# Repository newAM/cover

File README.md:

# Cover

A controller to automate my window shades.

This project is from late 2020; much older than the commit dates indicate.  I revisited it to migrate the raspberry pi controller to NixOS and decided to document the project.

## Software

* [NixOS](https://nixos.org/) for the raspberry pi OS
* [KiCad](https://www.kicad.org/) (version 5) for PCB design
* [OpenSCAD](https://openscad.org/) for 3D printed parts

## Hardware

The hardware consists of:

* A raspberry pi
* A custom pi hat to drive motors
* A motor per shade
* Plastic 3D printed motor mounts
* Metal 3D printed grips
* Plastic 3D printed guides
* 2 reed switches on each shade for endstops

### Shades

The shades on my windows have a continuous ball chain string without any clasps.  The ball chain originally had some plastic stoppers on them, but these all broke off before this project due to UV exposure.

The windows have a clutch on them, I measured the force required to overcome this clutch by tieing a water bottle onto the ball chain, and filling it with water until the chain started to move.  The final weight of the water bottle was 2 kilos ∴ about 20N of force is required to move the shades.

### Motors

I purchased generic 12V motors online, if you search "DC 12V worm gear motor" you will find these easily at almost every retailer.  These had more than enough torque to overcome the 20N of the clutch.

I purchased 25 rpm motors, which was lower than I needed.  The grips ended up being a smaller diameter than I initially intended; which means the shades move slower than intended.

#### Grips

The grip is a metal 3D printed part with grooves for the ball chain.  I tried to make this in plastic, but the forces required always stripped plastic parts.

The intent was to make this part match the diameter of the clutch on my shades, but metal 3D printing is extremely expensive, and I ended up making the part much smaller to keep costs down.  Each part ended up costing $40 from [shapeways](https://www.shapeways.com/).

#### Mount

The mount screws onto the motor and has two large flat surfaces to mount the motor onto the wall with command strips.  I used command strips because I rent, but they were probably the best solution anyway.

### Endstops

The endstops consisted of two reed switches per window, one at the top of the frame, and one at the bottom.  I taped magnets onto the shades to trip the reed switches when the shades hit the limit.

3D printed mounts were necessary to raise the reed switches to the shades.

### Controller

The controller is just a hat on a raspberry pi with 6x inputs for reed switches, and 3x DRV8871DDAR motor drivers for the output.

If I had to do this project over I would have used an Ethernet connected microcontroller instead of a pi.  Upon boot the raspberry pi takes a few seconds to apply the GPIO configuration in `/boot/config.txt`, which is not desirable, as this can lead to the shades moving beyond their endstop positions.

The controller takes commands over MQTT for move up, move down, and stop.

I run [NixOS](https://nixos.org/) on the pi.  The only other configuration necessary is putting `gpio=5,12,6,13,19,16=op,dl` into `/boot/config.txt`:

```nix
{
  boot.loader.raspberryPi = {
    enable = true;
    version = n;
    firmwareConfig = ''
      gpio=5,12,6,13,19,16=op,dl
    '';
  };
}
```

The service is a simple python script that I am not very proud of because it is all blocking code with polling.  I plan to rewrite this at some point, but it keeps working so I keep putting it off.

## Home Assistant

Home-assistant has a [MQTT cover integration](https://www.home-assistant.io/integrations/cover.mqtt/) that works out of the box.

```nix
{
  services.home-assistant.config.cover = [
    {
      platform = "mqtt";
      name = "Middle Window";
      unique_id = "middle_window";
      command_topic = "/home/sunroom/middle_window/set";
      position_topic = "/home/sunroom/middle_window/position";
      optimistic = false;
      retain = false;
    }
    # ... other shades
  ];
}
```

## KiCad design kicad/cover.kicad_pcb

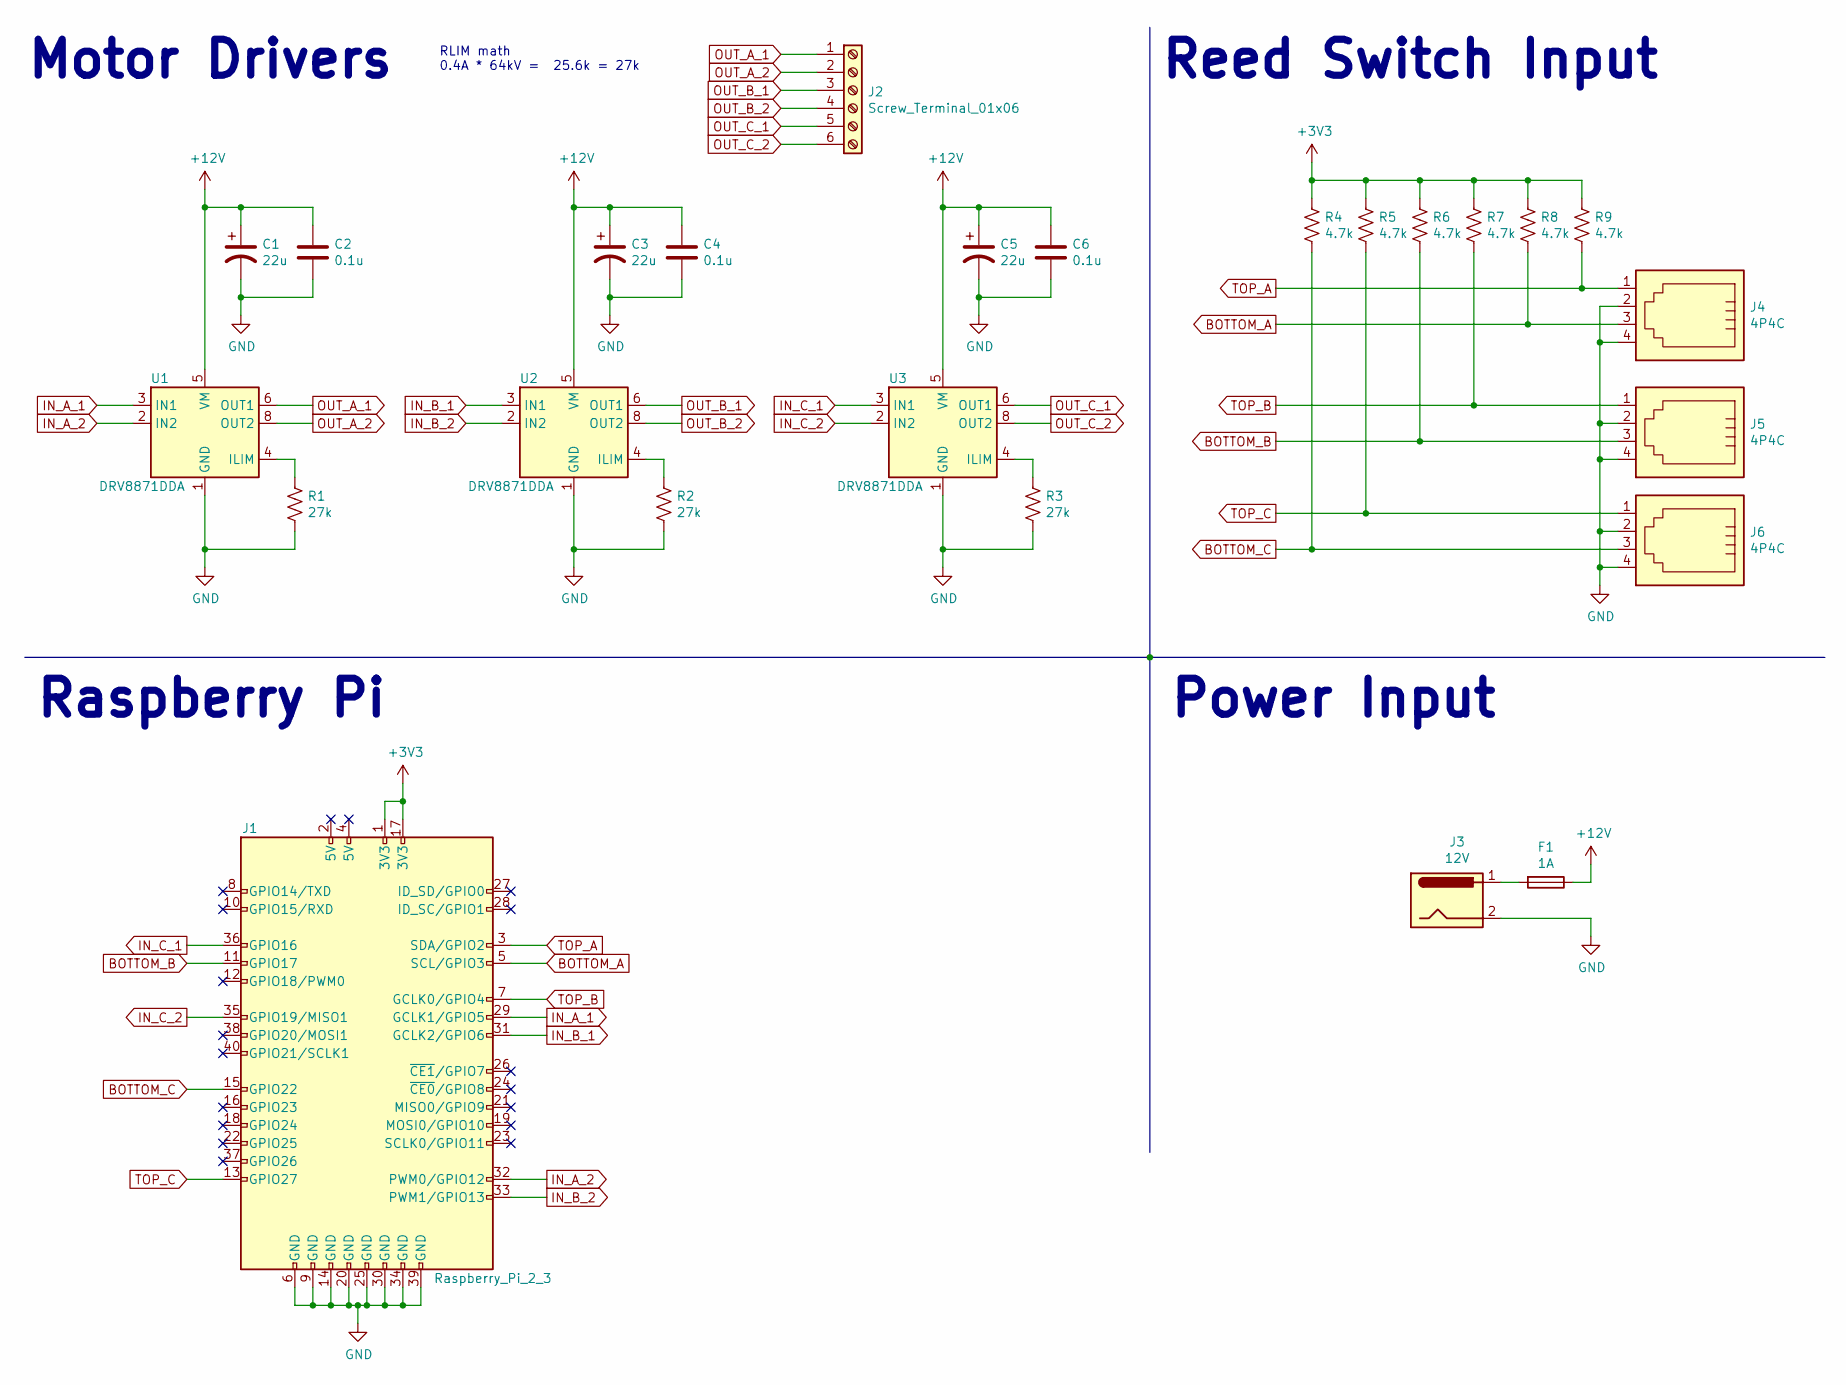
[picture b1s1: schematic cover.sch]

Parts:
C1, C3, C5: 22u; CP_Radial_D5.0mm_P2.00mm
C2, C4, C6: 0.1u; C_0603_1608Metric
F1: 1A; Fuseholder_Cylinder-5x20mm_Schurter_0031_8201_Horizontal_Op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
J1: Raspberry_Pi_2_3; PinHeader_2x20_P2.54mm_Vertical
J2: Screw_Terminal_01x06; TerminalBlock_Phoenix_MKDS-1,5-6_1x06_P5.00mm_Horizontal
J3: 12V; BarrelJack_CUI_PJ-102AH_Horizontal
J4, J5, J6: 4P4C; A-2004-3-4-LP-N-R
R1, R2, R3: 27k; R_0603_1608Metric
R4, R5, R6, R7, R8, R9: 4.7k; R_0603_1608Metric
U1, U2, U3: DRV8871DDA; Texas_HTSOP-8-1EP_3.9x4.9mm_P1.27mm_EP2.95x4.9mm_Mask2.4x3.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

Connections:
+3V3: J1.1 (3V3), J1.17 (3V3), R4.1, R5.1, R6.1, R7.1, R8.1, R9.1
+12V: C1.1, C2.1, C3.1, C4.1, C5.1, C6.1, F1.1, U1.5 (VM), U2.5 (VM), U3.5 (VM)
BOTTOM_A: J1.5 (SCL/GPIO3), J4.3, R8.2
BOTTOM_B: J1.11 (GPIO17), J5.3, R6.2
BOTTOM_C: J1.15 (GPIO22), J6.3, R4.2
GND: C1.2, C2.2, C3.2, C4.2, C5.2, C6.2, J1.6 (GND), J1.9 (GND), J1.14 (GND), J1.20 (GND), J1.25 (GND), J1.30 (GND), J1.34 (GND), J1.39 (GND), J3.2, J4.2, J4.4, J5.2, J5.4, J6.2, J6.4, R1.2, R2.2, R3.2, U1.1 (GND), U1.7 (GND), U1.9 (GND), U2.1 (GND), U2.7 (GND), U2.9 (GND), U3.1 (GND), U3.7 (GND), U3.9 (GND)
IN_A_1: J1.29 (GCLK1/GPIO5), U1.3 (IN1)
IN_A_2: J1.32 (PWM0/GPIO12), U1.2 (IN2)
IN_B_1: J1.31 (GCLK2/GPIO6), U2.3 (IN1)
IN_B_2: J1.33 (PWM1/GPIO13), U2.2 (IN2)
IN_C_1: J1.36 (GPIO16), U3.3 (IN1)
IN_C_2: J1.35 (GPIO19/MISO1), U3.2 (IN2)
unnamed: F1.2, J3.1
unnamed: R1.1, U1.4 (ILIM)
unnamed: R2.1, U2.4 (ILIM)
unnamed: R3.1, U3.4 (ILIM)
OUT_A_1: J2.1, U1.6 (OUT1)
OUT_A_2: J2.2, U1.8 (OUT2)
OUT_B_1: J2.3, U2.6 (OUT1)
OUT_B_2: J2.4, U2.8 (OUT2)
OUT_C_1: J2.5, U3.6 (OUT1)
OUT_C_2: J2.6, U3.8 (OUT2)
TOP_A: J1.3 (SDA/GPIO2), J4.1, R9.2
TOP_B: J1.7 (GCLK0/GPIO4), J5.1, R7.2
TOP_C: J1.13 (GPIO27), J6.1, R5.2

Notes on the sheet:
RLIM math 0.4A * 64kV = 25.6k = 27k
Motor Drivers
Reed Switch Input
Raspberry Pi
Power Input

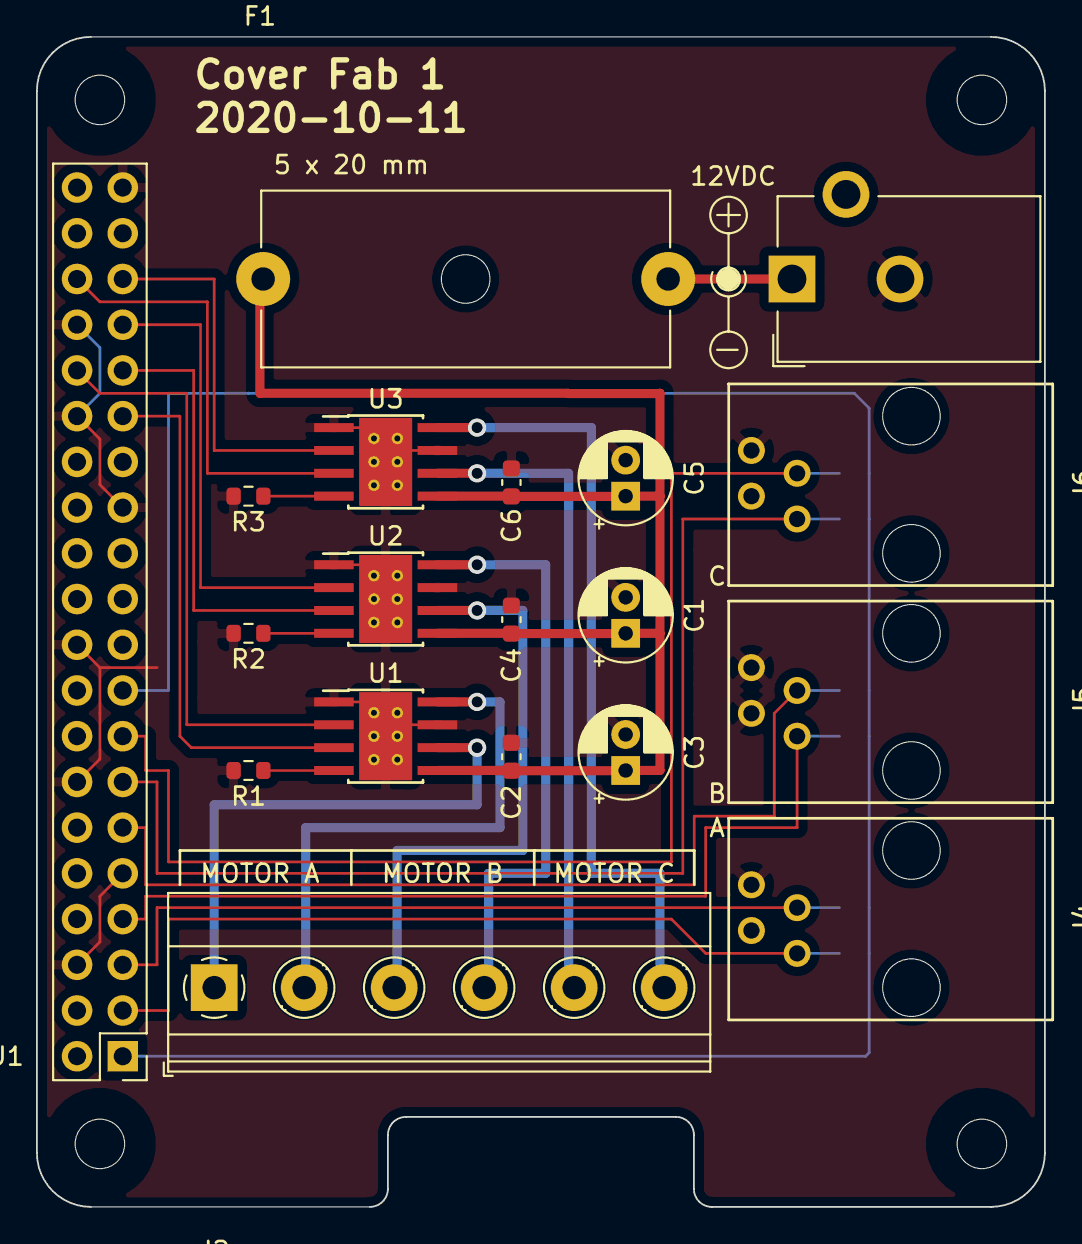
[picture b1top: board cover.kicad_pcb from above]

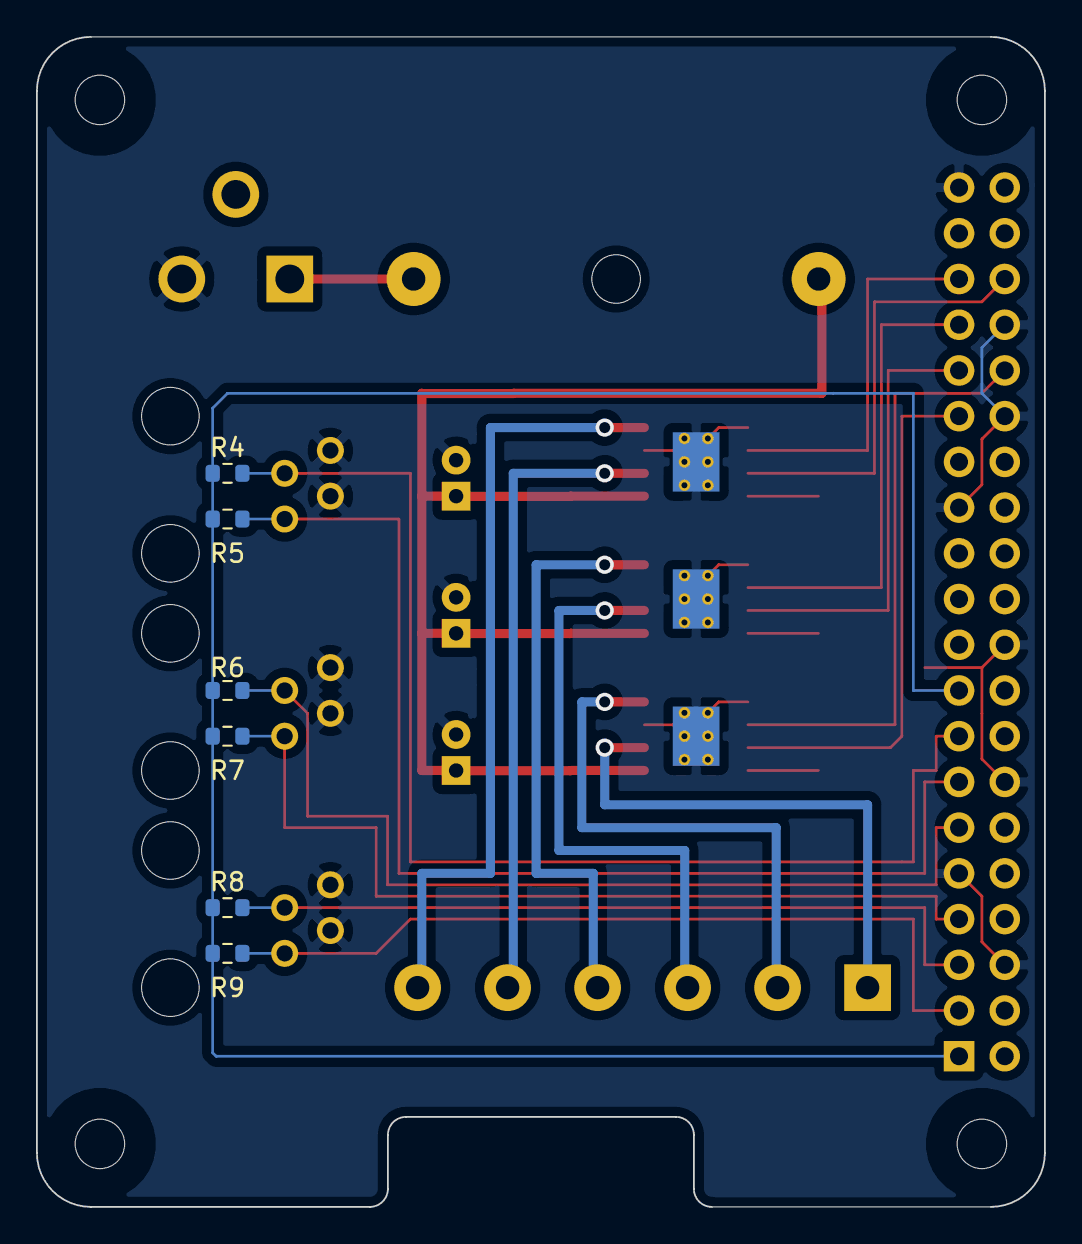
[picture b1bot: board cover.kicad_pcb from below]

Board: 2 copper layers, 56.0 x 65.0 mm, 25 parts (6 on the bottom side), 25 nets.

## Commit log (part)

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2022-08-20 flake: minor cleanup
2022-08-20 flake: fix cover binary
2022-08-20 Fix all sorts of problems with a Pi 3B+ on NixOS 22.05
2022-08-21 Add TLS to MQTT connection
2022-10-12 flake.nix: fix systemd-python build
2022-10-12 CI: fix aarch64 builds
2022-10-12 build(deps): bump cachix/install-nix-action from 17 to 18
    Bumps [cachix/install-nix-action](https://github.com/cachix/install-nix-action) from 17 to 18.
    - [Release notes](https://github.com/cachix/install-nix-action/releases)
    - [Commits](https://github.com/cachix/install-nix-action/compare/v17...v18)
    ---
    updated-dependencies:
    - dependency-name: cachix/install-nix-action
2022-10-13 CI: bump cachix actions
2022-10-29 flake.lock: update
    • Updated input 'nixpkgs':
    'github:nixos/nixpkgs/34c5293a71ffdb2fe054eb5288adc1882c1eb0b1' (2022-10-09)
    → 'github:nixos/nixpkgs/448a599c49978c2794401bfc3a2e1fba1a8663be' (2022-10-28)
2022-11-19 flake.nix: reproducibly reference top-level directory
2022-12-03 increase timeouts
2023-01-13 flake.lock, poetry.lock: update
    • Updated input 'nixpkgs':
    'github:nixos/nixpkgs/b72b8b94cf0c012b0252a9100a636cad69696666' (2022-12-02)
    → 'github:nixos/nixpkgs/6c8644fc37b6e141cbfa6c7dc8d98846c4ff0c2e' (2023-01-11)
    updated setuptools 65.6.3 -> 65.7.0
2023-01-20 build(deps): bump setuptools from 66.0.0 to 66.1.1
    Bumps [setuptools](https://github.com/pypa/setuptools) from 66.0.0 to 66.1.1.
    - [Release notes](https://github.com/pypa/setuptools/releases)
    - [Changelog](https://github.com/pypa/setuptools/blob/main/CHANGES.rst)
    - [Commits](https://github.com/pypa/setuptools/compare/v66.0.0...v66.1.1)
    ---
    updated-dependencies:
2023-02-01 build(deps): bump setuptools from 66.1.1 to 67.1.0
    Bumps [setuptools](https://github.com/pypa/setuptools) from 66.1.1 to 67.1.0.
    - [Release notes](https://github.com/pypa/setuptools/releases)
    - [Changelog](https://github.com/pypa/setuptools/blob/main/CHANGES.rst)
    - [Commits](https://github.com/pypa/setuptools/compare/v66.1.1...v67.1.0)
    ---
    updated-dependencies:
2023-02-13 build(deps): bump systemd-python from 234 to 235
    Bumps [systemd-python](https://github.com/systemd/python-systemd) from 234 to 235.
    - [Release notes](https://github.com/systemd/python-systemd/releases)
    - [Changelog](https://github.com/systemd/python-systemd/blob/main/NEWS)
    - [Commits](https://github.com/systemd/python-systemd/compare/v234...v235)
    ---
    updated-dependencies:
2023-02-15 build(deps): bump setuptools from 67.3.1 to 67.3.2
    Bumps [setuptools](https://github.com/pypa/setuptools) from 67.3.1 to 67.3.2.
    - [Release notes](https://github.com/pypa/setuptools/releases)
    - [Changelog](https://github.com/pypa/setuptools/blob/main/CHANGES.rst)
    - [Commits](https://github.com/pypa/setuptools/compare/v67.3.1...v67.3.2)
    ---
    updated-dependencies:
2023-02-21 build(deps): bump setuptools from 67.3.3 to 67.4.0
    Bumps [setuptools](https://github.com/pypa/setuptools) from 67.3.3 to 67.4.0.
    - [Release notes](https://github.com/pypa/setuptools/releases)
    - [Changelog](https://github.com/pypa/setuptools/blob/main/CHANGES.rst)
    - [Commits](https://github.com/pypa/setuptools/compare/v67.3.3...v67.4.0)
    ---
    updated-dependencies:
2023-03-06 build(deps): bump setuptools from 67.4.0 to 67.5.1
    Bumps [setuptools](https://github.com/pypa/setuptools) from 67.4.0 to 67.5.1.
    - [Release notes](https://github.com/pypa/setuptools/releases)
    - [Changelog](https://github.com/pypa/setuptools/blob/main/CHANGES.rst)
    - [Commits](https://github.com/pypa/setuptools/compare/v67.4.0...v67.5.1)
    ---
    updated-dependencies:
2023-03-28 build(deps): bump setuptools from 67.6.0 to 67.6.1
    Bumps [setuptools](https://github.com/pypa/setuptools) from 67.6.0 to 67.6.1.
    - [Release notes](https://github.com/pypa/setuptools/releases)
    - [Changelog](https://github.com/pypa/setuptools/blob/main/CHANGES.rst)
    - [Commits](https://github.com/pypa/setuptools/compare/v67.6.0...v67.6.1)
    ---
    updated-dependencies:
2023-04-21 build(deps): bump setuptools from 67.7.0 to 67.7.1
    Bumps [setuptools](https://github.com/pypa/setuptools) from 67.7.0 to 67.7.1.
    - [Release notes](https://github.com/pypa/setuptools/releases)
    - [Changelog](https://github.com/pypa/setuptools/blob/main/CHANGES.rst)
    - [Commits](https://github.com/pypa/setuptools/compare/v67.7.0...v67.7.1)
    ---
    updated-dependencies:
2023-04-25 flake.lock, poetry.lock: update
    • Updated input 'nixpkgs':
    'github:nixos/nixpkgs/6c8644fc37b6e141cbfa6c7dc8d98846c4ff0c2e' (2023-01-11)
    → 'github:nixos/nixpkgs/884ac294018409e0d1adc0cae185439a44bd6b0b' (2023-04-24)
    updated setuptools 67.7.1 -> 67.7.2
2023-06-16 build(deps): bump cachix/install-nix-action from 21 to 22
    Bumps [cachix/install-nix-action](https://github.com/cachix/install-nix-action) from 21 to 22.
    - [Release notes](https://github.com/cachix/install-nix-action/releases)
    - [Commits](https://github.com/cachix/install-nix-action/compare/v21...v22)
    ---
    updated-dependencies:
    - dependency-name: cachix/install-nix-action
2023-06-19 build(deps): bump setuptools from 67.8.0 to 68.0.0
    Bumps [setuptools](https://github.com/pypa/setuptools) from 67.8.0 to 68.0.0.
    - [Release notes](https://github.com/pypa/setuptools/releases)
    - [Changelog](https://github.com/pypa/setuptools/blob/main/CHANGES.rst)
    - [Commits](https://github.com/pypa/setuptools/compare/v67.8.0...v68.0.0)
    ---
    updated-dependencies:
2023-08-15 build(deps): bump setuptools from 68.0.0 to 68.1.0
    Bumps [setuptools](https://github.com/pypa/setuptools) from 68.0.0 to 68.1.0.
    - [Release notes](https://github.com/pypa/setuptools/releases)
    - [Changelog](https://github.com/pypa/setuptools/blob/main/NEWS.rst)
    - [Commits](https://github.com/pypa/setuptools/compare/v68.0.0...v68.1.0)
    ---
    updated-dependencies:
2023-08-18 build(deps): bump setuptools from 68.1.0 to 68.1.2
    Bumps [setuptools](https://github.com/pypa/setuptools) from 68.1.0 to 68.1.2.
    - [Release notes](https://github.com/pypa/setuptools/releases)
    - [Changelog](https://github.com/pypa/setuptools/blob/main/NEWS.rst)
    - [Commits](https://github.com/pypa/setuptools/compare/v68.1.0...v68.1.2)
    ---
    updated-dependencies:
2023-08-31 poetry.lock: update
    updated setuptools 68.1.0 -> 68.1.2
2023-09-04 build(deps): bump actions/checkout from 3 to 4
    Bumps [actions/checkout](https://github.com/actions/checkout) from 3 to 4.
    - [Release notes](https://github.com/actions/checkout/releases)
    - [Changelog](https://github.com/actions/checkout/blob/main/CHANGELOG.md)
    - [Commits](https://github.com/actions/checkout/compare/v3...v4)
    ---
    updated-dependencies:
2023-09-07 build(deps): bump setuptools from 68.1.2 to 68.2.0
    Bumps [setuptools](https://github.com/pypa/setuptools) from 68.1.2 to 68.2.0.
    - [Release notes](https://github.com/pypa/setuptools/releases)
    - [Changelog](https://github.com/pypa/setuptools/blob/main/NEWS.rst)
    - [Commits](https://github.com/pypa/setuptools/compare/v68.1.2...v68.2.0)
    ---
    updated-dependencies:
2023-10-02 build(deps): bump gpiozero from 1.6.2 to 2.0
    Bumps [gpiozero](https://github.com/gpiozero/gpiozero) from 1.6.2 to 2.0.
    - [Changelog](https://github.com/gpiozero/gpiozero/blob/master/docs/changelog.rst)
    - [Commits](https://github.com/gpiozero/gpiozero/compare/v1.6.2...v2.0)
    ---
    updated-dependencies:
    - dependency-name: gpiozero
2023-11-01 poetry2nix: nixpkgs -> flake
2023-11-02 Fix aarch64-linux package on x86_64-linux
2023-11-20 build(deps): bump setuptools from 68.2.2 to 69.0.0
    Bumps [setuptools](https://github.com/pypa/setuptools) from 68.2.2 to 69.0.0.
    - [Release notes](https://github.com/pypa/setuptools/releases)
    - [Changelog](https://github.com/pypa/setuptools/blob/main/NEWS.rst)
    - [Commits](https://github.com/pypa/setuptools/compare/v68.2.2...v69.0.0)
    ---
    updated-dependencies:
2023-11-28 build(deps): bump cachix/install-nix-action from 23 to 24
    Bumps [cachix/install-nix-action](https://github.com/cachix/install-nix-action) from 23 to 24.
    - [Release notes](https://github.com/cachix/install-nix-action/releases)
    - [Commits](https://github.com/cachix/install-nix-action/compare/v23...v24)
    ---
    updated-dependencies:
    - dependency-name: cachix/install-nix-action
2023-12-25 build(deps): bump setuptools from 69.0.2 to 69.0.3
    Bumps [setuptools](https://github.com/pypa/setuptools) from 69.0.2 to 69.0.3.
    - [Release notes](https://github.com/pypa/setuptools/releases)
    - [Changelog](https://github.com/pypa/setuptools/blob/main/NEWS.rst)
    - [Commits](https://github.com/pypa/setuptools/compare/v69.0.2...v69.0.3)
    ---
    updated-dependencies:
2024-02-12 build(deps): bump setuptools from 69.0.3 to 69.1.0
    Bumps [setuptools](https://github.com/pypa/setuptools) from 69.0.3 to 69.1.0.
    - [Release notes](https://github.com/pypa/setuptools/releases)
    - [Changelog](https://github.com/pypa/setuptools/blob/main/NEWS.rst)
    - [Commits](https://github.com/pypa/setuptools/compare/v69.0.3...v69.1.0)
    ---
    updated-dependencies:
2024-02-15 build(deps): bump gpiozero from 2.0 to 2.0.1
    Bumps [gpiozero](https://github.com/gpiozero/gpiozero) from 2.0 to 2.0.1.
    - [Changelog](https://github.com/gpiozero/gpiozero/blob/master/docs/changelog.rst)
    - [Commits](https://github.com/gpiozero/gpiozero/compare/v2.0...v2.0.1)
    ---
    updated-dependencies:
    - dependency-name: gpiozero
2024-03-12 flake.lock: update
    • Updated input 'nixpkgs':
    'github:nixos/nixpkgs/f9d39fb9aff0efee4a3d5f4a6d7c17701d38a1d8' (2024-02-11)
    → 'github:nixos/nixpkgs/3030f185ba6a4bf4f18b87f345f104e6a6961f34' (2024-03-09)
    • Updated input 'poetry2nix':
    'github:nix-community/poetry2nix/4eb2ac54029af42a001c9901194e9ce19cbd8a40' (2024-02-06)
    → 'github:nix-community/poetry2nix/3c92540611f42d3fb2d0d084a6c694cd6544b609' (2024-02-22)
2024-03-12 build(deps): bump paho-mqtt from 1.6.1 to 2.0.0
    Bumps [paho-mqtt](https://github.com/eclipse/paho.mqtt.python) from 1.6.1 to 2.0.0.
    - [Release notes](https://github.com/eclipse/paho.mqtt.python/releases)
    - [Changelog](https://github.com/eclipse/paho.mqtt.python/blob/master/ChangeLog.txt)
    - [Commits](https://github.com/eclipse/paho.mqtt.python/compare/v1.6.1...v2.0.0)
    ---
    updated-dependencies:
2024-03-12 build(deps): bump cachix/install-nix-action from 25 to 26
    Bumps [cachix/install-nix-action](https://github.com/cachix/install-nix-action) from 25 to 26.
    - [Release notes](https://github.com/cachix/install-nix-action/releases)
    - [Commits](https://github.com/cachix/install-nix-action/compare/v25...v26)
    ---
    updated-dependencies:
    - dependency-name: cachix/install-nix-action
2024-03-31 remove poetry2nix dependency
2024-03-31 flake.nix: fix gpiozero build error
2024-05-15 build(deps): bump cachix/install-nix-action from 26 to 27
    Bumps [cachix/install-nix-action](https://github.com/cachix/install-nix-action) from 26 to 27.
    - [Release notes](https://github.com/cachix/install-nix-action/releases)
    - [Commits](https://github.com/cachix/install-nix-action/compare/v26...V27)
    ---
    updated-dependencies:
    - dependency-name: cachix/install-nix-action
2024-05-20 poetry.lock, flake.lock: update
    updated setuptools 69.2.0 -> 69.5.1
    updated zipp 3.18.1 -> 3.18.2
    • Updated input 'nixpkgs':
    'github:nixos/nixpkgs/d8fe5e6c92d0d190646fb9f1056741a229980089' (2024-03-29)
    → 'github:nixos/nixpkgs/6c0b7a92c30122196a761b440ac0d46d3d9954f1' (2024-05-19)
